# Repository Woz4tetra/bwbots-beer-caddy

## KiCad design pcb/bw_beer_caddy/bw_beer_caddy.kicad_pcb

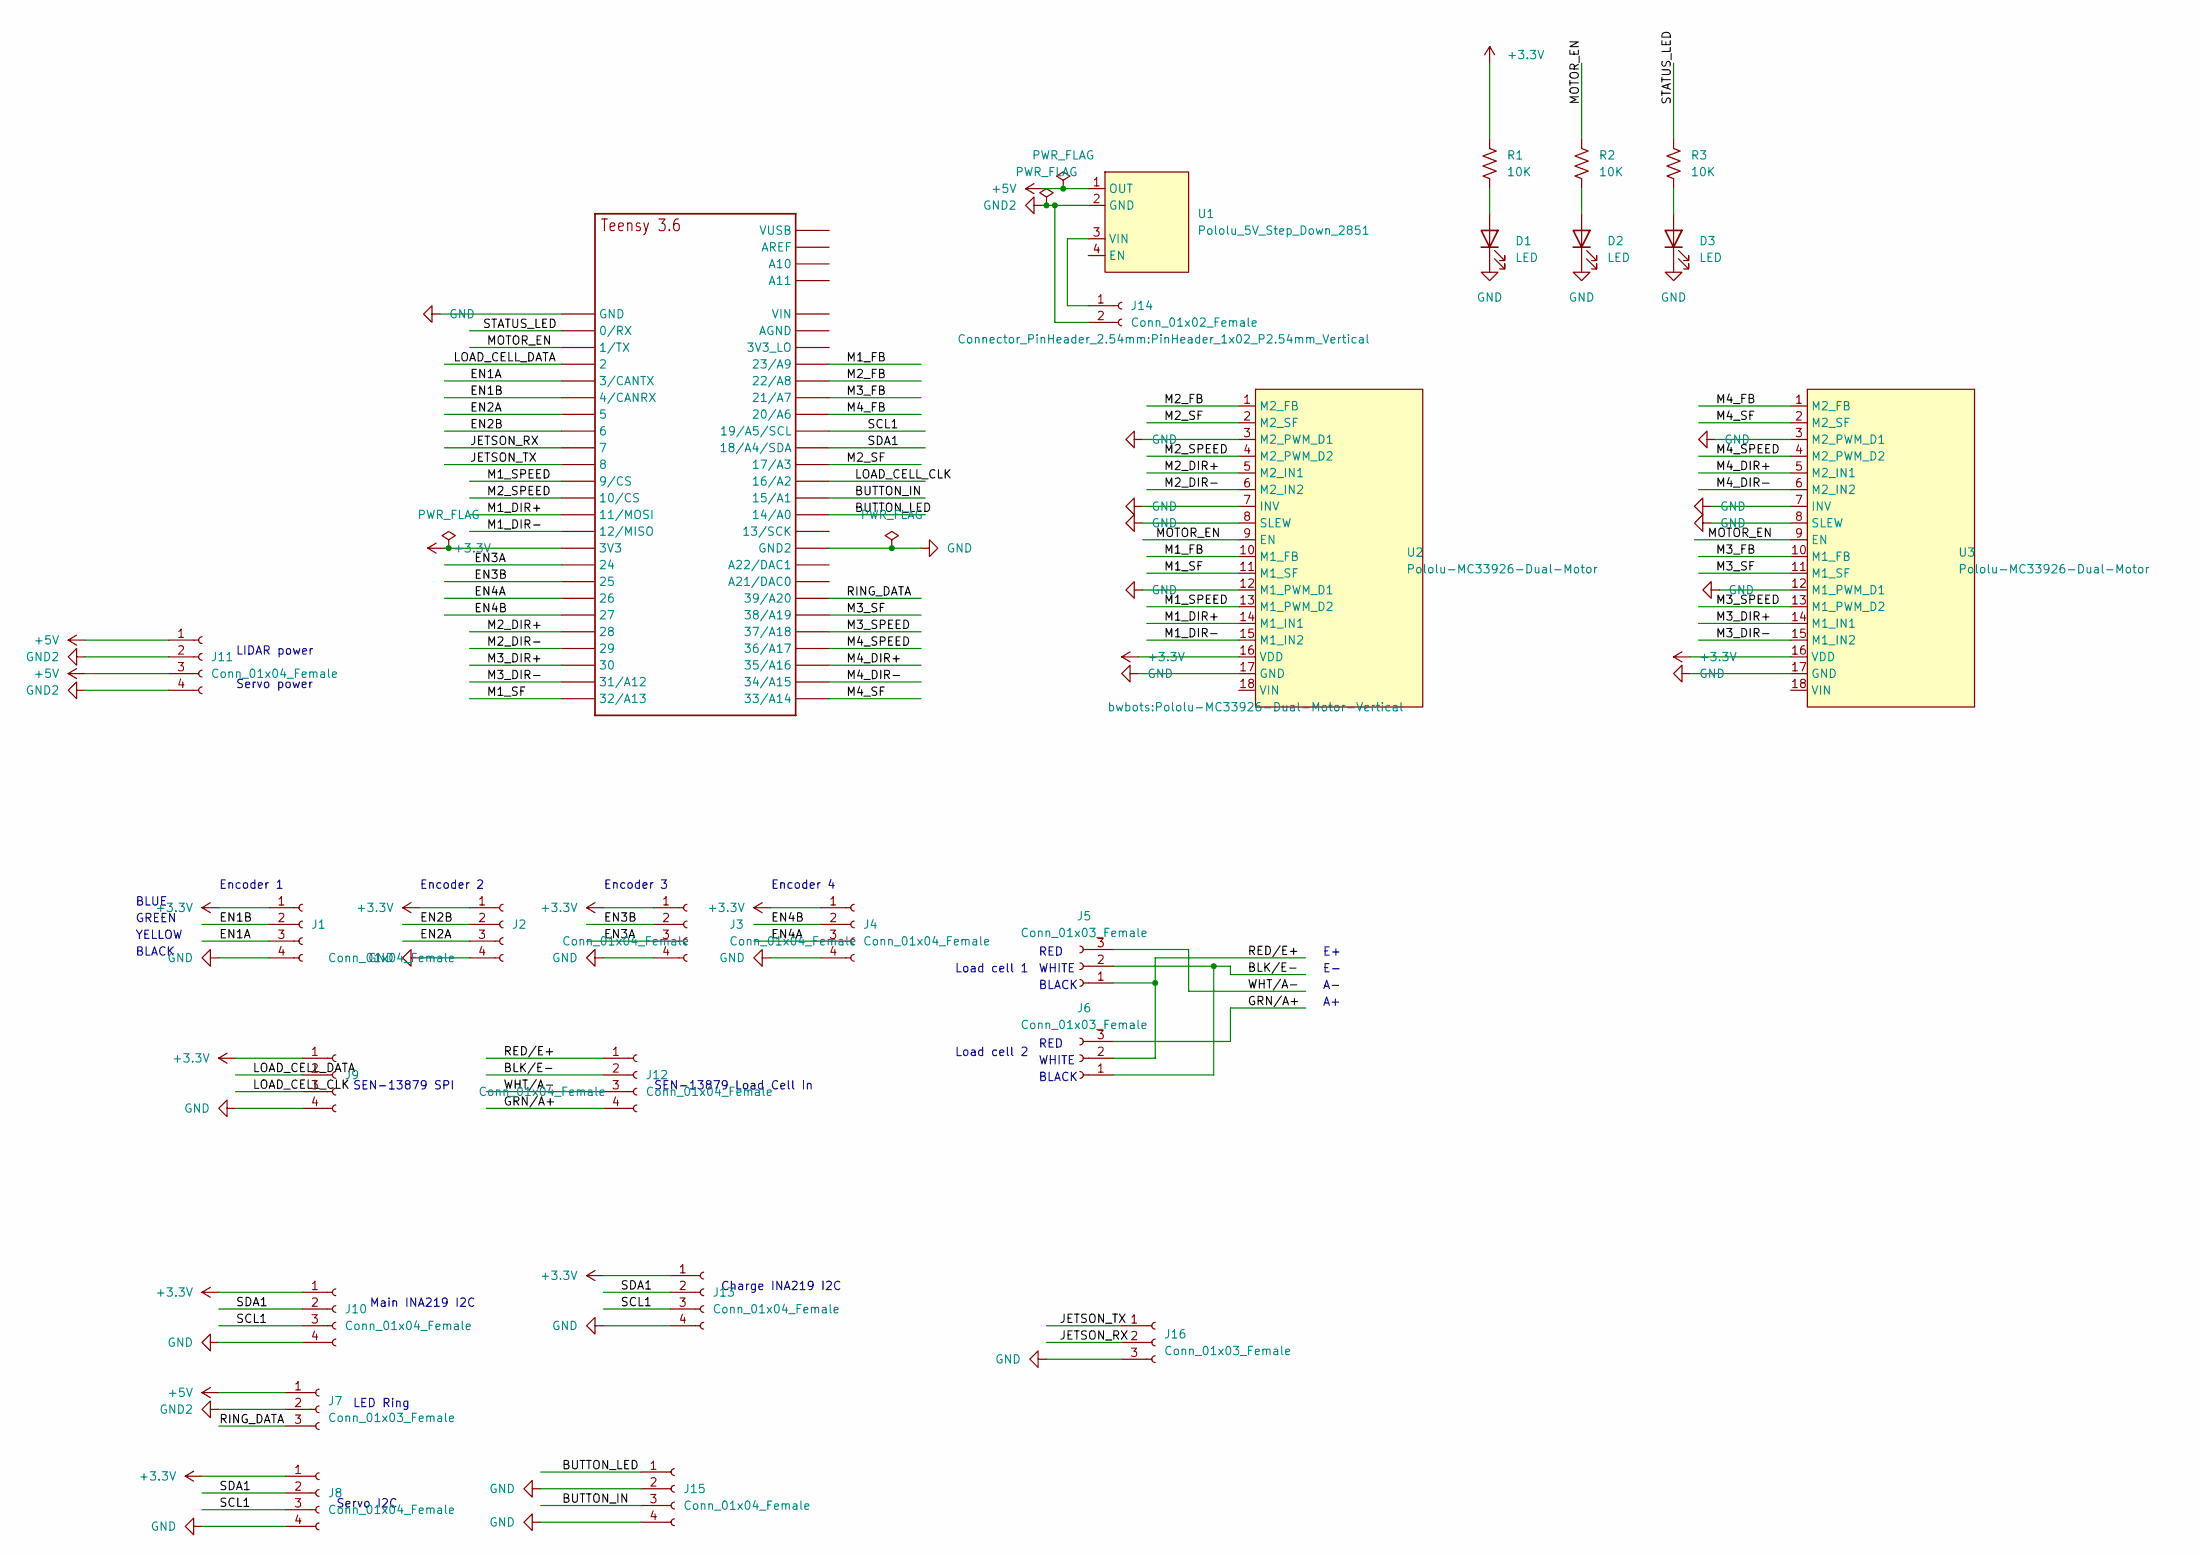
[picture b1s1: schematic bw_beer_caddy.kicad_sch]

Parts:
D1, D2, D3: LED; LED_1206_3216Metric; Part Number 1078
J1, J2, J3, J4, J8, J9, J10, J12, J13, J15: Conn_01x04_Female; JST_PH_B4B-PH-K_1x04_P2.00mm_Vertical
J5, J6, J7, J16: Conn_01x03_Female; JST_PH_B3B-PH-K_1x03_P2.00mm_Vertical; Part Number 1083
J11: Conn_01x04_Female; TerminalBlock_4Ucon_1x04_P3.50mm_Horizontal
J14: Conn_01x02_Female; PinHeader_1x02_P2.54mm_Vertical
R1, R2, R3: 10K; R_0805_2012Metric; Part Number 1090
U1: Pololu_5V_Step_Down_2851
U2, U3: Pololu-MC33926-Dual-Motor; Pololu-MC33926-Dual-Motor-Vertical
U$2: TEENSY_3.5{slash}3.6_BASIC; TEENSY_3.5_3.6_BASIC; Part Number 1099

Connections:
+3.3V: J1.1, J2.1, J3.1, J4.1, J8.1, J9.1, J10.1, J13.1, R1.2, U2.16 (VDD), U3.16 (VDD), U$2.3V3
+5V: J7.1, J11.1, J11.3, U1.1 (OUT)
/BLK/E-: J5.2, J6.1, J12.2
/BUTTON_IN: J15.3, U$2.15/A1
/BUTTON_LED: J15.1, U$2.14/A0
/EN1A: J1.3, U$2.3/CANTX
/EN1B: J1.2, U$2.4/CANRX
/EN2A: J2.3, U$2.5
/EN2B: J2.2, U$2.6
/EN3A: J3.3, U$2.24
/EN3B: J3.2, U$2.25
/EN4A: J4.3, U$2.26
/EN4B: J4.2, U$2.27
/GRN/A+: J6.3, J12.4
/JETSON_RX: J16.2, U$2.7
/JETSON_TX: J16.1, U$2.8
/LOAD_CELL_CLK: J9.3, U$2.16/A2
/LOAD_CELL_DATA: J9.2, U$2.2
/M1_DIR+: U2.14 (M1_IN1), U$2.11/MOSI
/M1_DIR-: U2.15 (M1_IN2), U$2.12/MISO
/M1_FB: U2.10 (M1_FB), U$2.23/A9
/M1_SF: U2.11 (M1_SF), U$2.32/A13
/M1_SPEED: U2.13 (M1_PWM_D2), U$2.9/CS
/M2_DIR+: U2.5 (M2_IN1), U$2.28
/M2_DIR-: U2.6 (M2_IN2), U$2.29
/M2_FB: U2.1 (M2_FB), U$2.22/A8
/M2_SF: U2.2 (M2_SF), U$2.17/A3
/M2_SPEED: U2.4 (M2_PWM_D2), U$2.10/CS
/M3_DIR+: U3.14 (M1_IN1), U$2.30
/M3_DIR-: U3.15 (M1_IN2), U$2.31/A12
/M3_FB: U3.10 (M1_FB), U$2.21/A7
/M3_SF: U3.11 (M1_SF), U$2.38/A19
/M3_SPEED: U3.13 (M1_PWM_D2), U$2.37/A18
/M4_DIR+: U3.5 (M2_IN1), U$2.35/A16
/M4_DIR-: U3.6 (M2_IN2), U$2.34/A15
/M4_FB: U3.1 (M2_FB), U$2.20/A6
/M4_SF: U3.2 (M2_SF), U$2.33/A14
/M4_SPEED: U3.4 (M2_PWM_D2), U$2.36/A17
/MOTOR_EN: R2.2, U2.9 (EN), U3.9 (EN), U$2.1/TX
/RED/E+: J5.1, J6.2, J12.1
/RING_DATA: J7.3, U$2.39/A20
/SCL1: J8.3, J10.3, J13.3, U$2.19/A5/SCL
/SDA1: J8.2, J10.2, J13.2, U$2.18/A4/SDA
/STATUS_LED: R3.2, U$2.0/RX
/WHT/A-: J5.3, J12.3
GND: D1.1 (K), D2.1 (K), D3.1 (K), J1.4, J2.4, J3.4, J4.4, J8.4, J9.4, J10.4, J13.4, J15.2, J15.4, J16.3, U2.3 (M2_PWM_D1), U2.7 (INV), U2.8 (SLEW), U2.12 (M1_PWM_D1), U2.17 (GND), U3.3 (M2_PWM_D1), U3.7 (INV), U3.8 (SLEW), U3.12 (M1_PWM_D1), U3.17 (GND), U$2.GND, U$2.GND2
GND2: J7.2, J11.2, J11.4, J14.2, U1.2 (GND)
unnamed: D1.2 (A), R1.1
unnamed: D2.2 (A), R2.1
unnamed: D3.2 (A), R3.1
unnamed: J14.1, U1.3 (VIN)

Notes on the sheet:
Encoder 3
Main INA219 I2C
Servo power
Load cell 2
GREEN
SEN-13879 SPI
Encoder 2
WHITE
YELLOW
BLACK
Servo I2C
RED
Load cell 1
BLUE
SEN-13879 Load Cell In
Encoder 4
Encoder 1
Charge INA219 I2C
LED Ring
LIDAR power

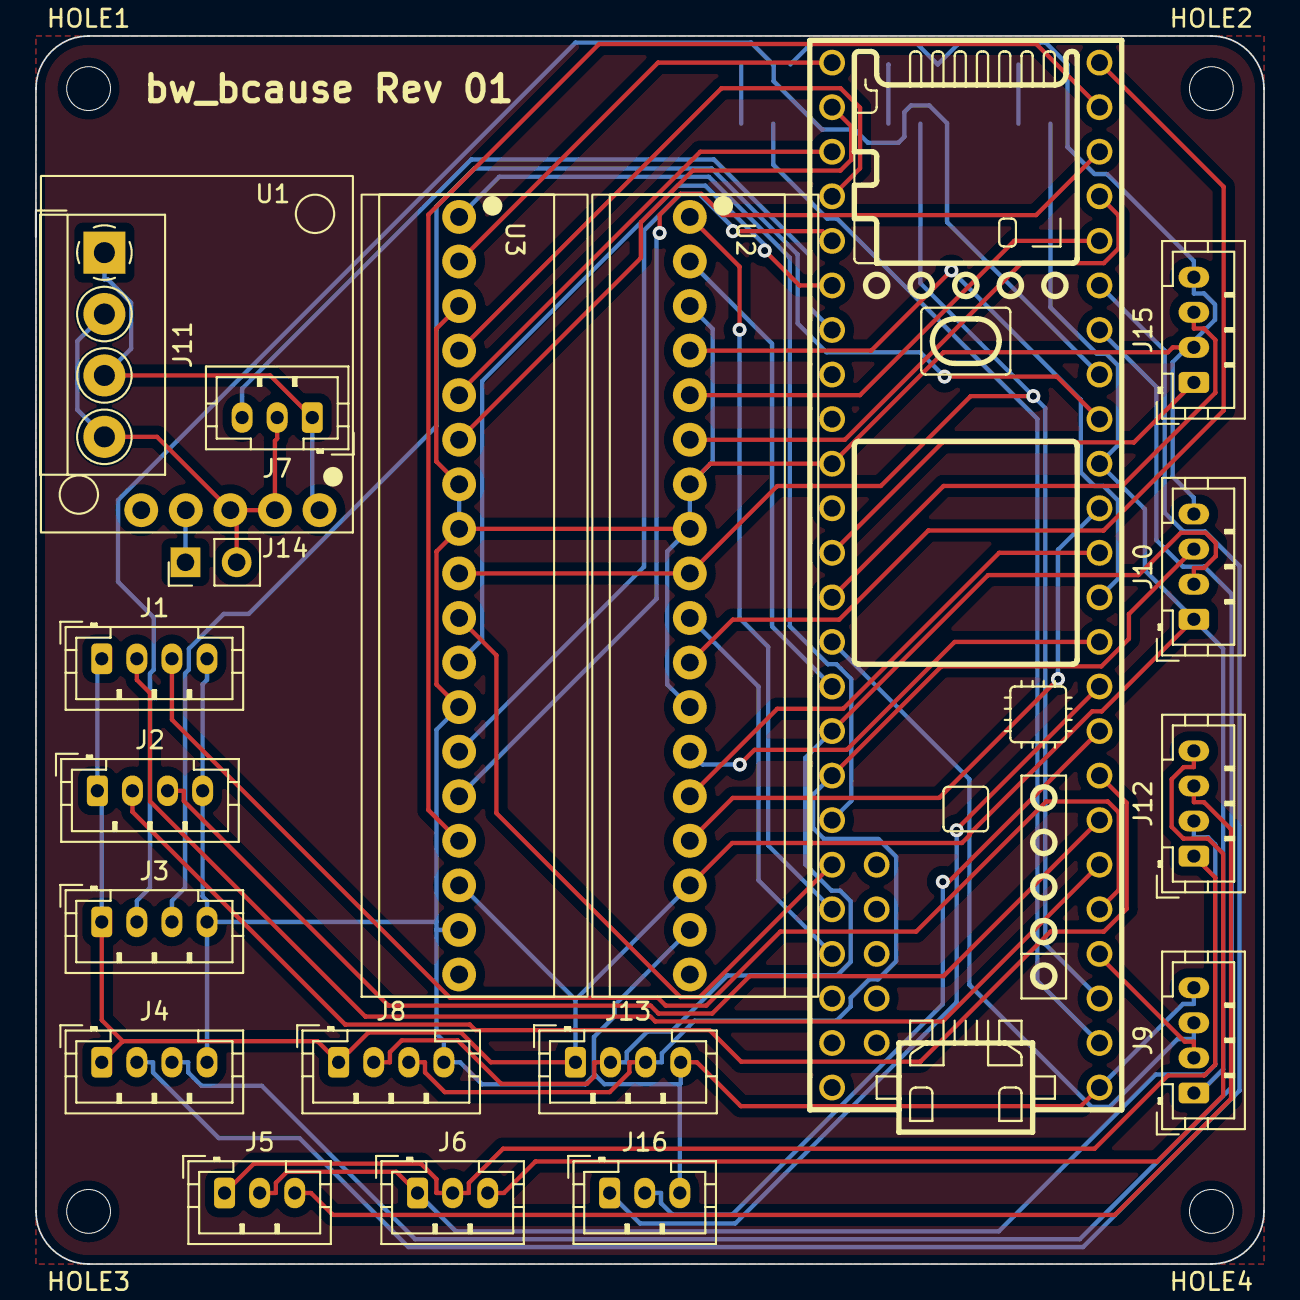
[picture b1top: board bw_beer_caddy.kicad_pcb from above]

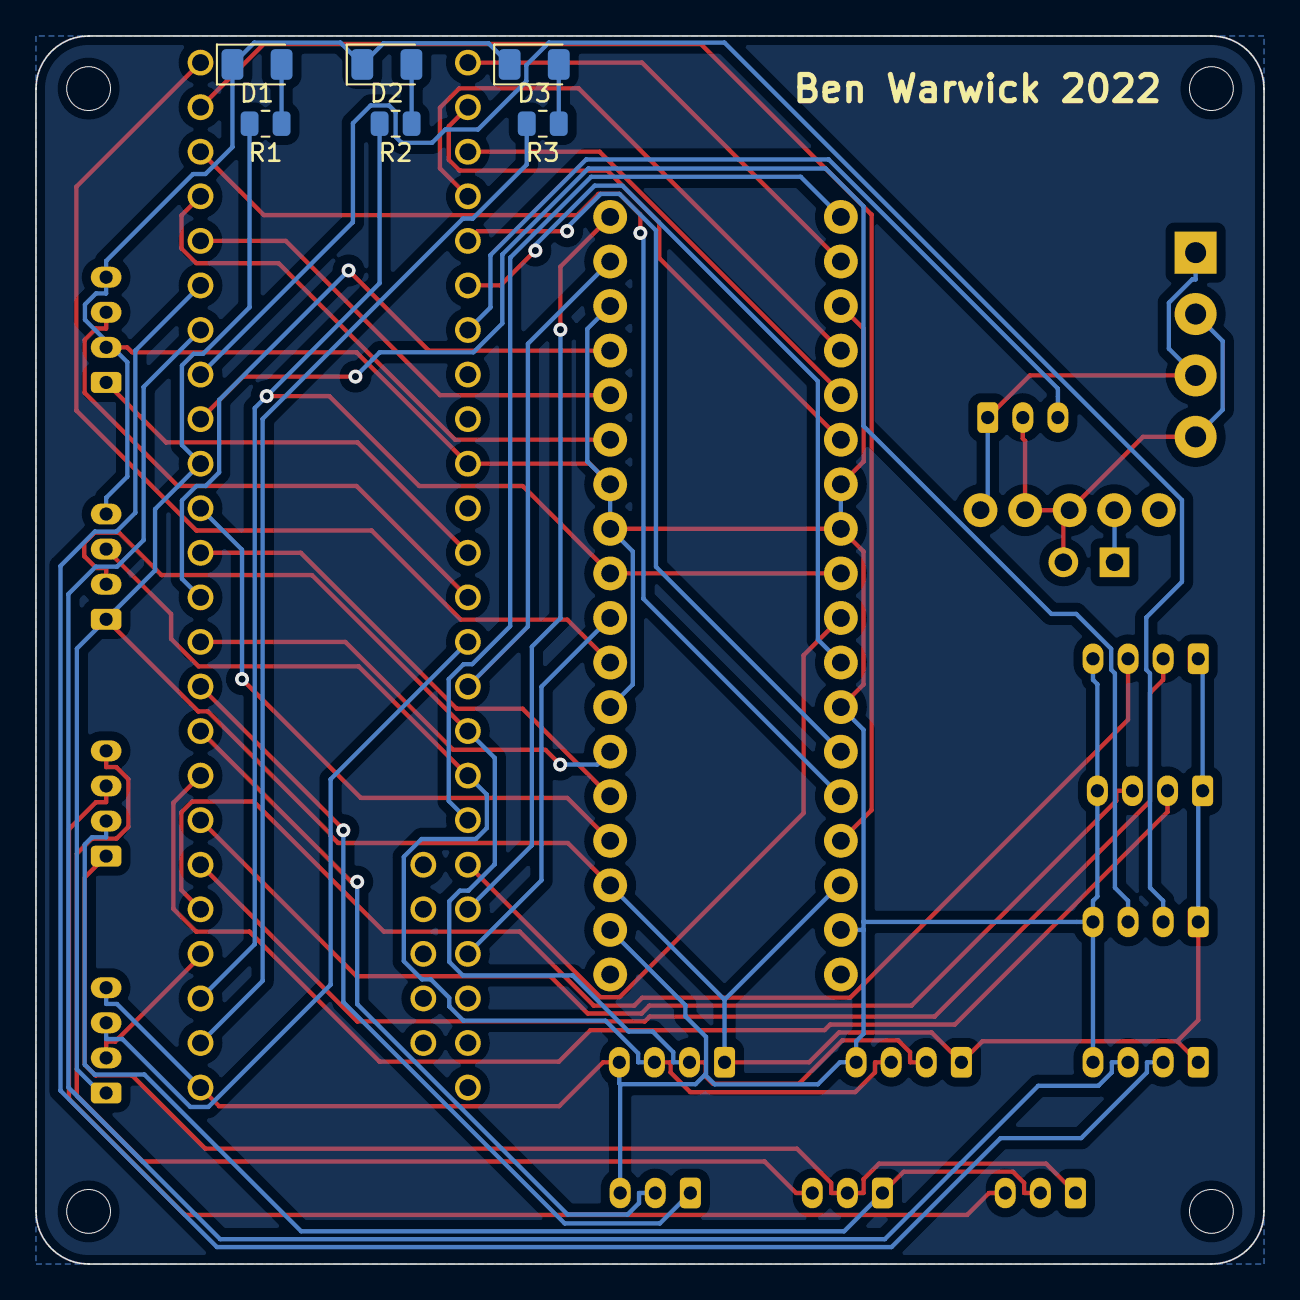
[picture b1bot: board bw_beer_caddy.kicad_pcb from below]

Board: 2 copper layers, 70.0 x 70.0 mm, 30 parts (6 on the bottom side), 51 nets.

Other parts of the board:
HOLE1, HOLE2, HOLE3, HOLE4: MountingHole_2.5mm

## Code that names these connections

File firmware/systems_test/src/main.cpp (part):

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
#define I2C_BUS_1 Wire

const int STATUS_LED = 0;
const int MOTOR_EN = 1;

const int BUTTON_IN = 15;
const int BUTTON_LED = 14;
const int BUILTIN_LED = 13;


const int M1_SPEED = 9;
const int M1_DIR_P = 11;
const int M1_DIR_N = 12;
const int M1_SF = 32;
const int M1_FB = 23;

const int M2_SPEED = 10;
const int M2_DIR_P = 28;
const int M2_DIR_N = 29;
const int M2_SF = 17;
const int M2_FB = 22;

const int M3_SPEED = 37;
const int M3_DIR_P = 30;
const int M3_DIR_N = 31;
const int M3_SF = 38;
const int M3_FB = 21;

const int M4_SPEED = 36;
const int M4_DIR_P = 35;
const int M4_DIR_N = 34;
const int M4_SF = 33;
const int M4_FB = 20;

MotorControllerMC33926 motor1(M1_SPEED, M1_DIR_P, M1_DIR_N, M1_SF, M1_FB);
MotorControllerMC33926 motor2(M2_SPEED, M2_DIR_P, M2_DIR_N, M2_SF, M2_FB);
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
    led_ring.begin();

    pinMode(STATUS_LED, OUTPUT);
    pinMode(MOTOR_EN, OUTPUT);

    pinMode(BUTTON_IN, INPUT_PULLUP);
    pinMode(BUTTON_LED, OUTPUT);
    pinMode(BUILTIN_LED, OUTPUT);

    set_status_led(true);
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
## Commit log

2022-07-09 basic tunnel communication working
2022-07-09 shutdown button. systemd
2022-07-09 systemd uninstall script
2022-07-10 untested motor and encoder control code
2022-07-10 motor control via command line is working
2022-07-10 tail script
2022-07-10 balance controller basic interface
2022-07-10 specific data type formats. IMU polling. base for controller finished
2022-07-12 matlab simulation for balance bot
2022-07-12 pd controller
2022-07-12 hooking up balance configs
2022-07-30 reorganizing
2022-07-31 bw_bcause rev 00 release
2022-08-01 add servo test command
2022-08-01 switching i2c bus
2022-08-22 pcb rev 01 08-21-2022
2022-08-22 rev 01 - fixing connectors
2022-08-22 creating folder in export
2022-08-23 moving connector
2022-08-23 moving leds
2022-09-01 testing firmware
2022-09-01 rev 01 pcb release
2022-09-08 encoder, chassis, and system test
2022-09-22 more tests
2022-09-22 rotate and straight demo works
2022-09-23 system test updates
2022-09-23 syntax fixes
2022-09-23 setup docs
2022-09-24 instructions
2022-09-24 systems test adjustments
2022-09-25 more of the driver implemented
2022-09-26 filled out module interface
2022-09-26 servo fixes
2022-09-26 flipping negatives correctly
2022-09-27 first pass at kinematics
2022-09-28 vx, vt kinematics working
2022-09-28 joystick -> tcp -> tunnel demo working
2022-09-28 refactor joystick
2022-09-28 add enable button
2022-09-28 add python logs to exclude
2022-09-29 strafing added
2022-09-29 odometry stubs
2022-09-30 odom prototype working
2022-09-30 found working PID constants. Many speed/unit fixes
2022-09-30 parameter adjustment. reporting power
2022-09-30 add ros install scripts
2022-09-30 docs change
2022-09-30 reorganized install. add odometry calculation on microcontroller
2022-09-30 blocking enable if battery is too low
2022-09-30 wrap enable method
2022-10-01 rename to ros1
2022-10-01 change to ros1
2022-10-01 add ros2 files
2022-10-01 fixing matrix pointer issue
2022-10-01 update Dockerfile
2022-10-01 fix entrypoint
2022-10-01 change zed image to jetson
2022-10-03 fix robot install instructions. add odom distance calculations. restoring voltage disable. add charge detect
2022-10-03 instruction fixes. remove aiopubsub dependency
2022-10-03 ros1 install changes. add description, interfaces, viz
2022-10-03 systemd fixes. Install fixes. add tunnel, rplidar, laser slam
2022-10-03 flipping right module models
2022-10-03 workstation instruction change
2022-10-04 build fixes
2022-10-04 laser slam working
2022-10-04 moving tunnel to submodule. add load cell firmware
2022-10-04 remove libdeps
2022-10-04 pid changes
2022-10-04 tunnel update
2022-10-05 load cell node added
2022-10-05 load cell working. adding 64 bit messages
2022-10-05 fix deploy script. add load cell to bringup
2022-10-05 add yolo and zed
2022-10-05 attempt at complete ros2 dockerfile
2022-10-06 docker file second attempt
2022-10-06 ros2 docker is working. Need to add other packages
2022-10-06 instruction change
2022-10-06 adding cylone config just in case
2022-10-06 bw_description builds
2022-10-06 load cell calibration
2022-10-07 attempting to fix velocity issues. Fixed curvature bug
2022-10-10 fixing command kinematics and PWM exponent issues
2022-10-10 increase kick deadzone command
2022-10-10 removing non ascii characters
2022-10-11 auto driving works
2022-10-13 tune AMCL, move_base. setting systemd to start after network and time sync
2022-10-14 disable automatically after a few seconds. Add midi song player
2022-10-19 sequencer functional. add handshake and get packets
2022-10-19 better path planning parameters
2022-10-19 starting unity simulator
2022-10-19 add QuickOutline
2022-10-20 fixing midi tempo issues
2022-10-20 fix get result segfault
2022-10-20 last sequence script
2022-10-20 simulator setup instructions
2022-10-20 saving unity project
2022-10-21 robot no longer falls through the floor
2022-10-21 robot moves
2022-10-21 save scene
2022-10-22 add tags, launcher. creating laser scan for obstacles
2022-10-22 reducing camera resolution
2022-11-01 light sequencer
2022-11-01 light sequence improvements. sequences from flash working
2022-11-01 serial restart bug fixes
2022-11-01 generating new map
2022-11-01 cleaning up startup sequence
2022-11-01 more light sequences. first pass at waypoints
2022-11-03 bw_waypoints overhaul. First behavior/action added
2022-11-03 find tag action
2022-11-04 finished first pass of actions
2022-11-04 using enum
2022-11-04 add action test scripts
2022-11-04 waypoint bug fixes. go to waypoint action is working
2022-11-04 small script change
2022-11-05 fixing go to pose and waypoint
2022-11-05 reversable go to pose. more sequences
2022-11-05 attempts to fix go to pose
2022-11-06 go to pose working. add light show to midi player
2022-11-06 zed toggling attempts
2022-11-06 fixing up find tag
2022-11-06 find tag is working
2022-11-07 combing tag and go to pose
2022-11-07 dock routine almost working. Attempting to fix serial issues
2022-11-10 swapping serial buses
2022-11-10 cleaning up dock test
2022-11-10 hold module positions in last commanded position instead of returning to zero all the time
2022-11-10 changing sequence scripts
2022-11-11 improving turning in place losses
2022-11-11 redo map. amcl and dwa parameter updates. attempt to fix auto dock
2022-11-12 implemented sequence action
2022-11-12 publish tags all the time
2022-11-12 improving tag finder
2022-11-16 docking works with new bumpers
2022-11-16 adjusting DWA parameters
2022-11-16 script param change
2022-11-17 dock routine improvements. firmware tweaks. redo map
2022-11-17 dock and mb param changes
2022-11-18 attempt at bts
2022-11-18 switch from blackboard to manager
2022-11-20 behavior tree test is working
2022-11-20 bts work for docking and undocking. Add voltage compensation and fix backwards steering
2022-11-20 add global speed pids for better move_base performance. refine dock bts
2022-11-21 reorganize main. Add button sequencer
2022-11-21 fixing driving bug
2022-11-21 button debounce and counter
2022-12-05 lots of planning, localization, and behavior improvements
2022-12-07 messing with hotspot settings
2022-12-08 syntax fixes. add docker for ros1
2022-12-08 splitting into native and cross compile
2022-12-10 docker improvements
2022-12-11 docker is functional
2022-12-11 capturing stop signal correctly
2022-12-12 add missions
2022-12-12 tag metadata fixes. behavior fixes
2022-12-13 starting dataset prep
2022-12-16 refreshing dataset builders and scripts
2022-12-17 modifiying for full body identification
2022-12-17 tag generator script
2022-12-17 fixing resume training
2022-12-18 add test script
2022-12-18 bts fixes. add person model. add kalman
2022-12-18 found new parameters for kalman odom
2022-12-18 better odom params
2022-12-18 better dock parameters
2022-12-18 fix tag stored frame bug
2022-12-19 almost got simulator working
2022-12-20 reorganized unity folder
2022-12-20 parameter tweaks
2022-12-20 found working parameters
2022-12-20 better controls. sensors and accessories
2022-12-20 trying scenes
2022-12-20 ROS connector. Laser publisher
2022-12-20 improving kinematics. new model. more sensors
2022-12-20 change message name to be less confusing
2022-12-20 Add website to monorepo
2022-12-21 Update styling
2022-12-21 Send deliver messages
2022-12-21 Send drink mission messages (#2)
    * Update styling
    * Send deliver messages
2022-12-22 fixing simulated kinematics. velocity control
2022-12-23 better odom filtering. starting to add dispenser and tags
2022-12-23 scene changes
2022-12-23 simulated dock and undock working
2022-12-24 unity docs refined camera controls
2022-12-24 fix image links
2022-12-24 better instructions
2022-12-24 saving scene
2022-12-24 add ground truth control to simulation
2022-12-24 small settings changes
2022-12-25 mission behavior is working
2022-12-25 start dispenser firmware
2022-12-26 more dispenser functionality
2023-01-03 setup for workstation docker image
2023-01-03 updating instructions
2023-01-03 move clone script for native build
2023-01-03 instruction fix
2023-01-04 implemented follow person behavior. Not tested
2023-01-04 add person detection messages
2023-01-05 fix camera object null point exception. fix native docker env
2023-01-05 full delivery routine complete in simulation
2023-01-05 add rqt py trees dependency
2023-01-06 applying correct mass properties
2023-01-06 fix iteration size change bug
2023-01-06 docker for webapp
2023-01-06 webapp mission works
2023-01-10 move workstation docker to unity
2023-01-11 add simulated point cloud
2023-01-11 add simulated cloud noise
2023-01-15 change to label topic
2023-01-15 new sequences. charge warning
2023-01-16 improved controller performance
2023-01-16 small fixes for dispense attempt
2023-01-18 add dev container
2023-01-18 colorful container prompts
2023-01-21 add gdb. switch zed wrapper branch
2023-01-21 fix in active action bug
2023-01-28 webapp docker container
2023-01-31 drive calibration generator
2023-02-05 drive calibration pole is working
2023-02-05 more calibration script prep
2023-02-06 refactor go to pose
2023-02-06 some fixes
2023-02-08 fix rotate in place behavior
2023-02-11 more attempts at fixing math
2023-02-11 add pose read out to sim
2023-02-13 getting closer
2023-02-14 found root cause. it was bad odometry calculation in combiner
2023-02-14 angle wrap manager
2023-02-14 go to pose is working
2023-02-16 ran some tests
2023-02-16 add als_ros
2023-02-20 fix dock issues
2023-02-20 drive to pose hang fix
2023-02-23 fixing lots of behaviors
2023-02-23 parameter adjustment
2023-02-23 new dispenser strategy
2023-02-23 adjust camera to real position
2023-02-23 define camera offset in description
2023-02-24 dock routine improvements
2023-02-24 add sequence playing
2023-02-25 better wheel velocity performance
2023-02-28 reduce charge threshold. upgrade to ZED SDK 3.8. switch to neural depth
2023-03-03 update to use new sensors
2023-03-03 mqtt test working
2023-03-03 add mqtt client to node
2023-03-03 reorganize function headers
2023-04-01 reorganize files for install
2023-04-01 rework docker
2023-04-01 docker fixes
2023-04-01 build on robot works
2023-04-01 rework docker again
2023-04-01 fixed copy scripts. fixed linker bug
2023-04-02 routine is working
2023-04-02 add comments
2023-04-02 more comments
2023-04-04 fix docker scripts
2023-04-04 add inflate polygon
2023-04-06 compact limiter
2023-07-24 rework complete
2023-07-24 update docs. fix simulated containers
2023-07-24 fix platformio install
2023-07-24 simulation is running again
2023-08-09 fix user name issues
2023-08-09 docker script fixes
2023-08-09 fix sequence script
2023-08-15 docker fixes. add bw_filter
2023-08-15 fix launches. add set_robot
2023-08-15 small docker fixes
2023-09-07 many workstation docker improvements. add typing
2023-09-08 more docker fixes. temporarily restore bw_tags
2023-09-08 vs code setup
2023-09-08 last docker fix. launch fix
2023-09-19 adding hotspot
2023-09-19 script improvements
2023-09-20 fix workstation build
2023-09-20 enable behaviors launch
2023-09-21 add lights and music node
2023-09-25 remove old behaviors. fix settings. add foxglove
2023-09-25 add data files
2023-09-25 fix data excludes
2023-09-25 launch improvements
2023-09-28 implement yolo request mode
2023-09-28 add yolo launch
2023-09-28 request tags
2023-09-28 wait for insync images
2023-09-28 sync all images
2023-10-01 camera recording configs
2023-10-01 update dispenser firmware
2023-10-02 settable speed
2023-10-02 dispensing is working
2023-10-02 fixing up node
2023-10-02 watch for falling edge
2023-10-02 dispenser clean up
2023-10-02 prep behaviors package
2023-10-02 starting undock behavior
2023-10-02 refactor to structs
2023-10-02 time stamp bug fix
2023-10-07 simulation tweaks. Delete data scripts
2023-10-07 remove unused
2023-10-07 adjust camera
2023-10-08 simulated tag requests. waypoint teaching
2023-10-08 is charging check
2023-10-08 start dock behavior
2023-10-08 start optimizer navigation
2023-10-08 add optimizer
2023-10-08 simplier chassis optimizer
2023-10-08 try fixing optimizers
2023-10-10 first pass of spline controller
2023-11-05 modify docker for detectron
2023-11-05 attempt to fix dependencies
2023-11-05 adding files
2024-01-25 fix build for 2024
